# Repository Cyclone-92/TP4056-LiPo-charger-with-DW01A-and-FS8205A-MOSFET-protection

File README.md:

<h1 align="center">
  TP4056 with DW01 Protection Circuit
</h1>

## 📝 Overview

This is a 1A lithium battery charging and protection module that combines the TP4056 linear charger IC with DW01 protection IC. Perfect for safely charging and protecting single-cell Li-ion/Li-po batteries.

## 🔍 Module Details

| Front View | Back View | Schematic Layout |
|------------|-----------|------------|
|  |  |  |

## ⚡ Features

- **Charging Capabilities**:
  - Constant current/constant voltage operation
  - Programmable charge current up to 1A
  - Thermal regulation
  - Input voltage: 4.5-5.5V
  - Full charge voltage: 4.2V ±1%

- **Protection Features** (DW01):
  - ⚠️ Overcharge protection
  - 🔋 Over-discharge protection
  - ⚡ Short circuit protection
  - 🌡️ Overcurrent protection

- **Status Indicators**:
  - 🔴 Red LED   - Charging
  - 🔵 Blue LED  - Fully charged
  - ⚫ Both OFF  - No input power
 
## 🛠️ Example Projects

<details>
<summary>Power Bank Build</summary>
  1. Components needed:
    - TP4056 module
    - 18650 battery holder
    - USB ports
    - Case
</details>

<details>
<summary>Solar Charger</summary>
  1. Components needed:
    - TP4056 module
    - Solar panel (6V)
    - Battery
</details>

## ⚠️ Safety Warnings

```diff
- Only use with 3.7V Li-ion/Li-po batteries
- Do not exceed 5.5V input voltage
- Check battery polarity before connecting
- Not compatible with LiFePO4 batteries
- Keep away from moisture and extreme temperatures
```

<div align="center">
⭐ Star this repository if you find it helpful!
</div>

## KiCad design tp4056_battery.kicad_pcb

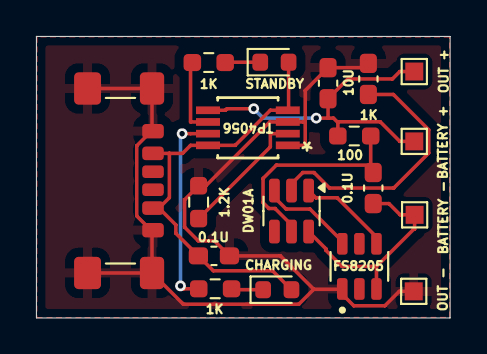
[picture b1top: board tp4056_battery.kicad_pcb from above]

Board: 2 copper layers, 23.0 x 15.6 mm, 18 parts (0 on the bottom side), 13 nets.

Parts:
C2, C3: 0.1U; C_0603_1608Metric_Pad1.08x0.95mm_HandSolder
C4: 10U; C_0603_1608Metric_Pad1.08x0.95mm_HandSolder
D2: STANDBY; LED_0603_1608Metric
D3: CHARGING; LED_0603_1608Metric
J1: USB_C_Receptacle_PowerOnly_6P; USB_C_Receptacle_GCT_USB4135-GF-A_6P_TopMnt_Horizontal
Q1: FS8205; SOT95P280X145-6N
R1, R3: 1K; R_0603_1608Metric_Pad0.98x0.95mm_HandSolder
R4: 1.2K; R_0603_1608Metric_Pad0.98x0.95mm_HandSolder
R5: 100; R_0603_1608Metric_Pad0.98x0.95mm_HandSolder
R6: 1K; C_0603_1608Metric_Pad1.08x0.95mm_HandSolder
TP1: BATTERY -; TestPoint_Pad_1.0x1.0mm
TP2: BATTERY +; TestPoint_Pad_1.0x1.0mm
TP3: OUT +; TestPoint_Pad_1.0x1.0mm
TP4: OUT -; TestPoint_Pad_1.0x1.0mm
U1: DW01A; SOT-23-6
U3: TP4056; TP4056-42-ESOP8_TPW

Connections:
GND: C2.2, C4.2, J1.A12 (GND), J1.B12 (GND), J1.S1 (SHIELD), Q1.1, R4.2, R6.2, TP4.1, U3.1 (TEMP), U3.3 (GND)
unnamed: C2.1, D2.2 (A), D3.2 (A), J1.A9 (VBUS), J1.B9 (VBUS), U3.4 (VCC), U3.8 (CE)
unnamed: D2.1 (K), R1.2
unnamed: D3.1 (K), R3.2
unnamed: R6.1, U1.2 (CS)
unnamed: C3.2, Q1.3, TP1.1, U1.6 (GND)
unnamed: Q1.6, U1.3 (OC)
unnamed: Q1.4, U1.1 (OD)
unnamed: C3.1, R5.2, U1.5 (VCC)
unnamed: R3.1, U3.7 (*CHRG)
unnamed: R1.1, U3.6 (*STDBY)
unnamed: C4.1, R5.1, TP2.1, TP3.1, U3.5 (BAT)
unnamed: R4.1, U3.2 (PROG)

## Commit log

2024-11-17 add images
